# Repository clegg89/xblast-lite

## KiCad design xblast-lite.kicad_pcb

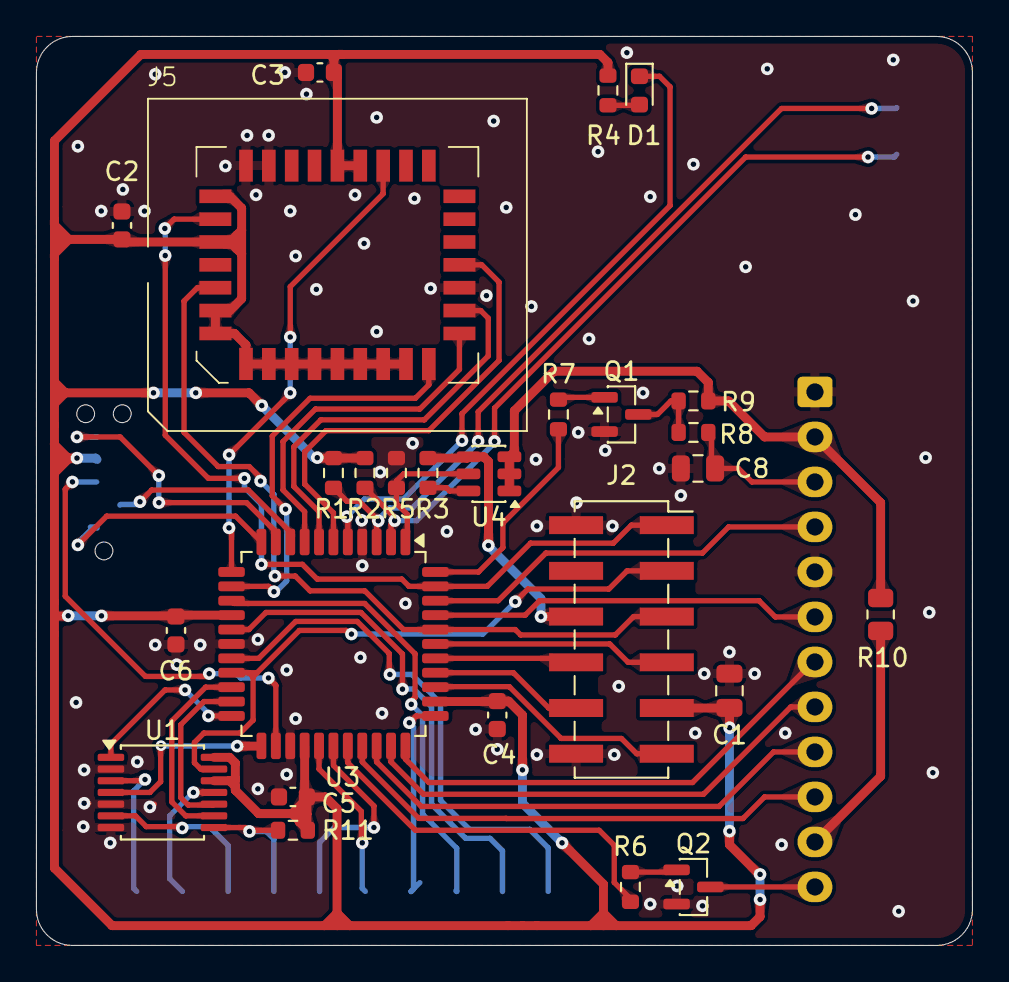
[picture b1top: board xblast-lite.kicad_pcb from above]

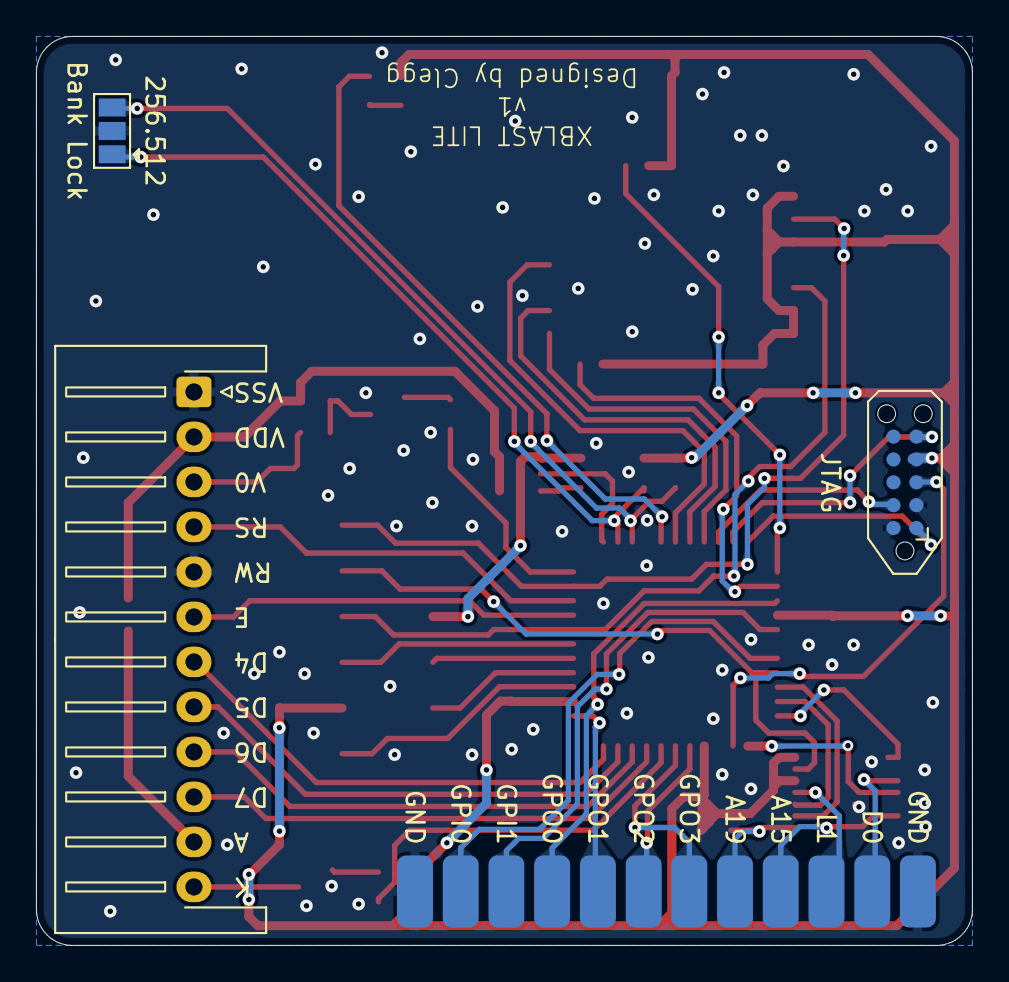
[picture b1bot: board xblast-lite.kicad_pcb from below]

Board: 2 copper layers, 52.0 x 50.5 mm, 30 parts (4 on the bottom side), 54 nets.

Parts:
C1, C8: 4.7u; C_0805_2012Metric
C2, C3, C4, C5, C6: 100nF; C_0603_1608Metric
D1: LED; LED_0603_1608Metric
J1: JTAG; Tag-Connect_TC2050-IDC-NL_2x05_P1.27mm_Vertical
J2: XBOX LPC; PinSocket_2x06_P2.54mm_Vertical_SMD
J3: GPIO; SolderWirePad_1x12_SMD_2x4mm
J4: LCD; JST_XH_S12B-XH-A-1_1x12_P2.50mm_Horizontal
J5: PLCC-32 Socket; PLCC-32_SMD-Socket
JP1: Bank Lock; SolderJumper-3_P1.3mm_Open_Pad1.0x1.5mm
Q1, Q2: BC846; SOT-23
R1, R2, R3, R5, R9, R11: 10k; R_0603_1608Metric
R4, R8: 1k; R_0603_1608Metric
R6, R7: 1.5k; R_0603_1608Metric
R10: 4.7; R_0805_2012Metric
U1: 74LVC125; TSSOP-14_4.4x5mm_P0.65mm
U3: XC9572XL-xxVQx44; TQFP-44_10x10mm_P0.8mm
U4: TPS27081A; SOT-23-6

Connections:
+3V3: C1.1, C2.2, C3.2, C4.1, C5.1, C6.1, J1.4, J2.9, J5.3, J5.4, J5.5, J5.6, J5.7, J5.8, J5.9, J5.10, J5.11, J5.12, J5.24, J5.25, J5.30, J5.32, R1.2, R2.2, R4.1, R11.1, U1.12, U1.14 (VCC), U3.15 (VCCINT), U3.26 (VCCIO), U3.35 (VCCINT)
+5V: J4.2, R9.2, R10.2, U4.1 (R2), U4.2 (VOUT), U4.3 (VOUT)
+5V_LPC: J2.6, R3.2, U4.4 (VIN)
/A15: J3.9, U1.6
/A15_CTRL: U1.4, U3.23 (I/O)
/A19: J3.8, R11.2, U1.8
/A19_CTRL: U1.10, U3.21 (I/O)
/A19_VAL: U1.9, U3.20 (I/O)
/BANK_SW0: JP1.1 (A), R2.1, U3.2 (I/O)
/BANK_SW1: JP1.3 (B), R1.1, U3.3 (I/O)
/D0: J3.11, U1.3
/D0_VAL: U1.1, U3.22 (I/O)
/EN_5V: R5.2, U3.1 (I/O/GCK3), U4.5 (ON/OFF)
/FLAD0: J5.13, U3.13 (I/O)
/FLAD1: J5.14, U3.8 (I/O)
/FLAD2: J5.15, U3.7 (I/O)
/FLAD3: J5.17, U3.6 (I/O)
/GPI0: J3.2, U3.18 (I/O)
/GPI1: J3.3, U3.16 (I/O)
/GPO0: J3.4, U3.14 (I/O)
/GPO1: J3.5, U3.34 (I/O/GTS2)
/GPO2: J3.6, U3.27 (I/O)
/GPO3: J3.7, U3.28 (I/O)
/L1: J3.10, U1.11
/LCD_BL: R6.1, U3.29 (I/O)
/LCD_BL_I: Q2.1 (B), R6.2
/LCD_BL_V: J4.11, R10.1
/LCD_CT: R7.1, U3.44 (I/O/GCK2)
/LCD_CT_I: Q1.1 (B), R7.2
/LCD_D4: J4.7, U3.33 (I/O/GSR)
/LCD_D5: J4.8, U3.32 (I/O)
/LCD_D6: J4.9, U3.31 (I/O)
/LCD_D7: J4.10, U3.30 (I/O)
/LCD_E: J4.6, U3.41 (I/O)
/LCD_Q1_CT: Q1.3 (C), R8.1, R9.1
/LCD_RS: J4.4, U3.42 (I/O)
/LCD_SW_BL: J4.12, Q2.3 (C)
/LCD_SW_CT: C8.1, J4.3, R8.2
/LDO_R1: R3.1, U4.6 (R1/C1)
/LED: D1.1 (K), U3.5 (I/O)
/LED_R: D1.2 (A), R4.2
/TCK: J1.1, U3.11 (TCK)
/TDI: J1.9, U3.9 (TDI)
/TDO: J1.3, U3.24 (TDO)
/TMS: J1.5, U3.10 (TMS)
/XLAD0: J2.11, U3.36 (I/O/GTS1)
/XLAD1: J2.10, U3.37 (I/O)
/XLAD2: J2.8, U3.38 (I/O)
/XLAD3: J2.7, U3.39 (I/O)
/XLCLK: J2.1, J5.31, U3.43 (I/O/GCK1)
/~FLFRAME: J5.23, U3.12 (I/O)
/~XLFRAME: J2.3, U1.13, U3.19 (I/O)
/~XLRESET: J2.5, J5.2, U3.40 (I/O)
GND: C1.2, C2.1, C3.1, C4.2, C5.2, C6.2, C8.2, J1.2, J1.10, J2.2, J2.12, J3.1, J3.12, J4.1, J4.5, J5.16, J5.28, J5.29, JP1.2 (C), Q1.2 (E), Q2.2 (E), R5.1, U1.2, U1.5, U1.7 (GND), U3.4 (GND), U3.17 (GND), U3.25 (GND)
